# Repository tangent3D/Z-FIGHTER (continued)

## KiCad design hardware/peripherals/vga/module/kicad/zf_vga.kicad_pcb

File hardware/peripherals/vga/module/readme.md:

## Z-FIGHTER VGA Module

[Project Notes](https://tangent.space/vga.htm)

[PCB schematic](../../../../media/schematic_vga_module.pdf)

[PCB layout](../../../../media/layout_vga_module.pdf)

## Bill of Materials
|Reference|Description|Mouser #|Link
|--|--|--|--|
U1,U2|74HC4040||
U3,U4|GAL16V8||
U5,U6,U12,U13,U14|74HC541||
U7|74HC00||
U8|74HC04||
U9|74HC74||
U10|74HC165||
U11|AS6C6264||
X1|25.175 MHz Oscillator, DIP8/DIP14||
Q1|BC547, TO-92||
R1 - R3|220Ω Resistor, 1/4W||
R4 - R8|75Ω Resistor, 1/4W||
R9,R10|1KΩ Resistor, 1/4W||
C1,C2,C3,C6,C7|470pF Capacitor, Ceramic, 5mm||
C4,C5|22pF Capacitor, Ceramic, 5mm||
C8 - C22|0.1uF Capacitor, Ceramic, 5mm||
J1|26P Female Header, Vertical||
J2|8P Female Header, Vertical||
J3|DE-15 Female R/A||
J4,J5|DE-9 Male R/A||
SW1|DIP Switch, 3x, 7.62mm||
JP1|Jumper, 2.54mm, Vertical||

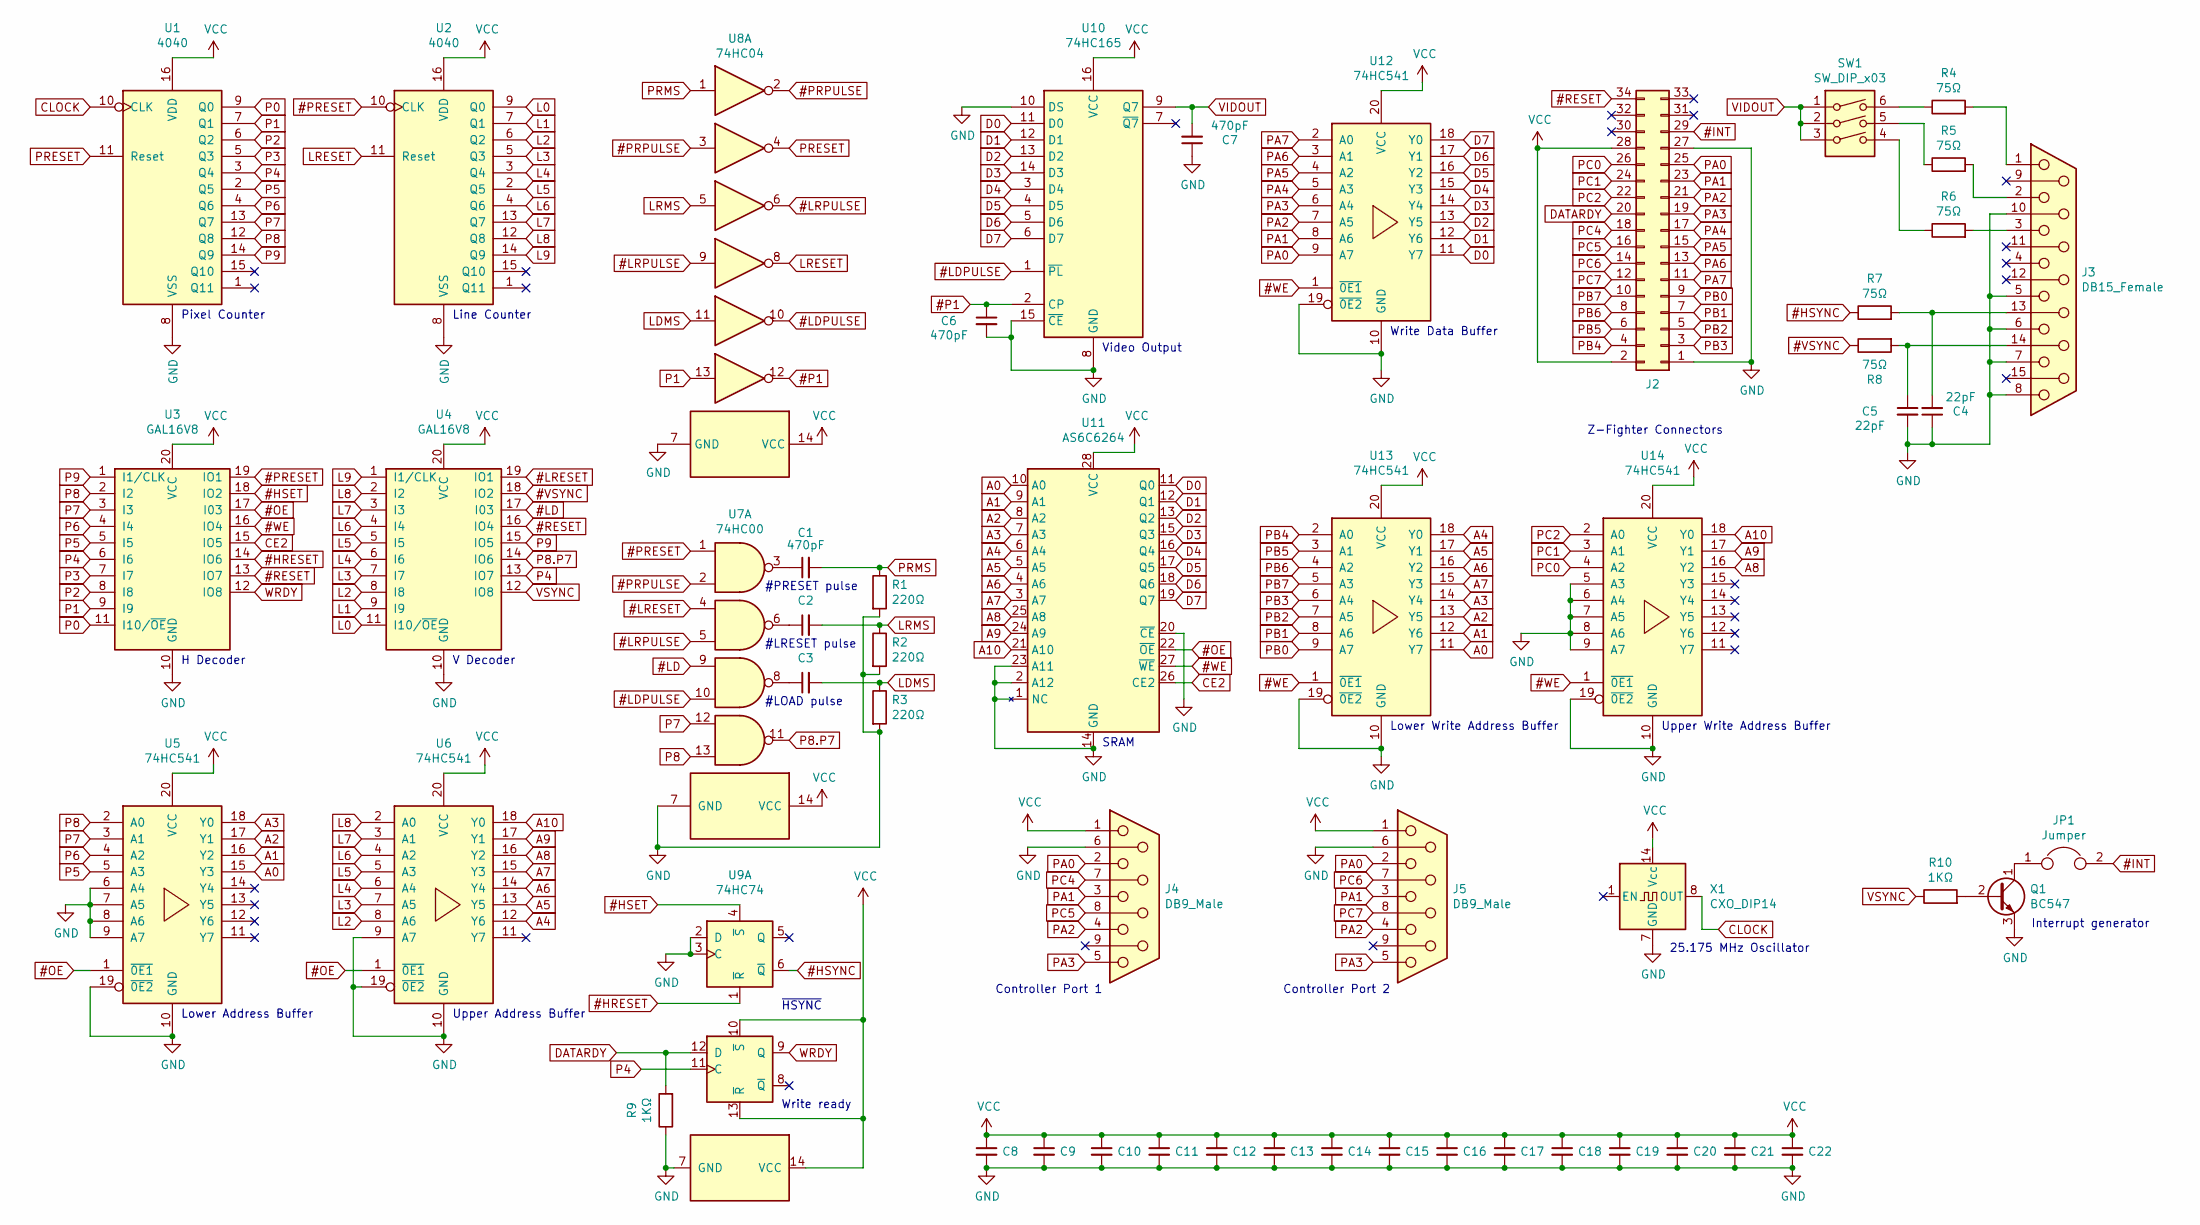
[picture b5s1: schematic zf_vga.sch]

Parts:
C1, C2, C3, C6, C7: 470pF; C_Disc_D7.5mm_W2.5mm_P5.00mm
C4, C5: 22pF; C_Disc_D7.5mm_W2.5mm_P5.00mm
C8, C9, C10, C11, C12, C13, C14, C15, C16, C17, C18, C19, C20, C21, C22: 0.1uF; C_Disc_D7.5mm_W2.5mm_P5.00mm
J2: Z-FIGHTER Expansion Port; Z-FIGHTER_Expansion_Port
J3: DB15_Female; DSUB-15-HD_Female_Horizontal_P2.29x1.98mm_EdgePinOffset8.35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
J4, J5: DB9_Male; DSUB-9_Male_Horizontal_P2.77x2.84mm_EdgePinOffset7.70mm_Hou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
JP1: Jumper
Q1: BC547; TO-92_Inline_Wide
R1, R2, R3: 220Ω; R_Axial_DIN0207_L6.3mm_D2.5mm_P7.62mm_Horizontal
R4, R5, R6, R7, R8: 75Ω; R_Axial_DIN0207_L6.3mm_D2.5mm_P7.62mm_Horizontal
R9, R10: 1KΩ; R_Axial_DIN0207_L6.3mm_D2.5mm_P7.62mm_Horizontal
SW1: SW_DIP_x03; DIP-6_W7.62mm_LongPads
U1, U2: 4040; DIP-16_W7.62mm_LongPads
U3, U4: GAL16V8; DIP-20_W7.62mm_LongPads
U5, U6, U12, U13, U14: 74HC541; DIP-20_W7.62mm_LongPads
U7: 74HC00; DIP-14_W7.62mm_LongPads
U8: 74HC04; DIP-14_W7.62mm_LongPads
U9: 74HC74; DIP-14_W7.62mm_LongPads
U10: 74HC165; DIP-16_W7.62mm_LongPads
U11: AS6C6264; DIP-28_W15.24mm_LongPads
X1: CXO_DIP14; Oscillator_DIP-14_LargePads

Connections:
#HRESET: U3.14 (IO6), U9.1 (~R)
#HSET: U3.18 (IO2), U9.4 (~S)
#HSYNC: R7.1, U9.6 (~Q)
#INT: J2.29, JP1.2
#LD: U4.17 (I03), U7.9
#LDPULSE: U7.10, U8.10, U10.1 (~PL)
#LRESET: U4.19 (IO1), U7.4
#LRPULSE: U7.5, U8.6, U8.9
#OE: U3.17 (I03), U5.1 (~0E1), U6.1 (~0E1), U11.22 (~OE)
#P1: C6.1, U8.12, U10.2 (CP)
#PRESET: U2.10 (CLK), U3.19 (IO1), U7.1
#PRPULSE: U7.2, U8.2, U8.3
#RESET: J2.34, U3.13 (IO7), U4.16 (IO4)
#VSYNC: R8.1, U4.18 (IO2)
#WE: U3.16 (IO4), U11.27 (~WE), U12.1 (~0E1), U13.1 (~0E1), U14.1 (~0E1)
A0: U5.15 (Y3), U11.10 (A0), U13.11 (Y7)
A1: U5.16 (Y2), U11.9 (A1), U13.12 (Y6)
A2: U5.17 (Y1), U11.8 (A2), U13.13 (Y5)
A3: U5.18 (Y0), U11.7 (A3), U13.14 (Y4)
A4: U6.12 (Y6), U11.6 (A4), U13.18 (Y0)
A5: U6.13 (Y5), U11.5 (A5), U13.17 (Y1)
A6: U6.14 (Y4), U11.4 (A6), U13.16 (Y2)
A7: U6.15 (Y3), U11.3 (A7), U13.15 (Y3)
A8: U6.16 (Y2), U11.25 (A8), U14.16 (Y2)
A9: U6.17 (Y1), U11.24 (A9), U14.17 (Y1)
A10: U6.18 (Y0), U11.21 (A10), U14.18 (Y0)
CE2: U3.15 (IO5), U11.26 (CE2)
CLOCK: U1.10 (CLK), X1.5, X1.8 (OUT); also elsewhere on the board
D0: U10.11 (D0), U11.11 (Q0), U12.11 (Y7)
D1: U10.12 (D1), U11.12 (Q1), U12.12 (Y6)
D2: U10.13 (D2), U11.13 (Q2), U12.13 (Y5)
D3: U10.14 (D3), U11.15 (Q3), U12.14 (Y4)
D4: U10.3 (D4), U11.16 (Q4), U12.15 (Y3)
D5: U10.4 (D5), U11.17 (Q5), U12.16 (Y2)
D6: U10.5 (D6), U11.18 (Q6), U12.17 (Y1)
D7: U10.6 (D7), U11.19 (Q7), U12.18 (Y0)
DATARDY: J2.20, R9.2, U9.12 (D)
GND: C4.1, C5.2, C6.2, C7.1, C8.2, C9.2, C10.2, C11.2, C12.2, C13.2, C14.2, C15.2, C16.2, C17.2, C18.2, C19.2, C20.2, C21.2, C22.2, J2.1, J2.27, J3.5, J3.6, J3.7, J3.8, J3.10, J4.6, J5.6, Q1.3 (E), R1.2, R2.2, R3.2, R9.1, U1.8 (VSS), U2.8 (VSS), U3.10 (GND), U4.10 (GND), U5.6 (A4), U5.7 (A5), U5.8 (A6), U5.9 (A7), U5.10 (GND), U5.19 (~0E2), U6.9 (A7), U6.10 (GND), U6.19 (~0E2), U7.7 (GND), U8.7 (GND), U9.2 (D), U9.3 (C), U9.7 (GND), U10.8 (GND), U10.10 (DS), U10.15 (~CE), U11.1 (NC), U11.2 (A12), U11.14 (GND), U11.20 (~CE), U11.23 (A11), U12.10 (GND), U12.19 (~0E2), U13.10 (GND), U13.19 (~0E2), U14.5 (A3), U14.6 (A4), U14.7 (A5), U14.8 (A6), U14.9 (A7), U14.10 (GND), U14.19 (~0E2), X1.4, X1.7 (GND); also elsewhere on the board
L0: U2.9 (Q0), U4.11 (I10/~OE~)
L1: U2.7 (Q1), U4.9 (I9)
L2: U2.6 (Q2), U4.8 (I8), U6.8 (A6)
L3: U2.5 (Q3), U4.7 (I7), U6.7 (A5)
L4: U2.3 (Q4), U4.6 (I6), U6.6 (A4)
L5: U2.2 (Q5), U4.5 (I5), U6.5 (A3)
L6: U2.4 (Q6), U4.4 (I4), U6.4 (A2)
L7: U2.13 (Q7), U4.3 (I3), U6.3 (A1)
L8: U2.12 (Q8), U4.2 (I2), U6.2 (A0)
L9: U2.14 (Q9), U4.1 (I1/CLK)
LDMS: C3.2, R3.1, U8.11
LRESET: U2.11 (Reset), U8.8
LRMS: C2.2, R2.1, U8.5
unnamed: C1.1, U7.3
unnamed: C2.1, U7.6
unnamed: C3.1, U7.8
unnamed: C4.2, J3.13, R7.2
unnamed: C5.1, J3.14, R8.2
unnamed: J3.1, R4.2
unnamed: J3.2, R5.2
unnamed: J3.3, R6.2
unnamed: JP1.1, Q1.1 (C)
unnamed: Q1.2 (B), R10.2
unnamed: R4.1, SW1.6
unnamed: R5.1, SW1.5
unnamed: R6.1, SW1.4
P0: U1.9 (Q0), U3.11 (I10/~OE~)
P1: U1.7 (Q1), U3.9 (I9), U8.13
P2: U1.6 (Q2), U3.8 (I8)
P3: U1.5 (Q3), U3.7 (I7)
P4: U1.3 (Q4), U3.6 (I6), U4.13 (IO7), U9.11 (C)
P5: U1.2 (Q5), U3.5 (I5), U5.5 (A3)
P6: U1.4 (Q6), U3.4 (I4), U5.4 (A2)
P7: U1.13 (Q7), U3.3 (I3), U5.3 (A1), U7.12
P8: U1.12 (Q8), U3.2 (I2), U5.2 (A0), U7.13
P8.P7: U4.14 (IO6), U7.11
P9: U1.14 (Q9), U3.1 (I1/CLK), U4.15 (IO5)
PA0: J2.25, J4.2, J5.2, U12.9 (A7)
PA1: J2.23, J4.3, J5.3, U12.8 (A6)
PA2: J2.21, J4.4, J5.4, U12.7 (A5)
PA3: J2.19, J4.5, J5.5, U12.6 (A4)
PA4: J2.17, U12.5 (A3)
PA5: J2.15, U12.4 (A2)
PA6: J2.13, U12.3 (A1)
PA7: J2.11, U12.2 (A0)
PB0: J2.9, U13.9 (A7)
PB1: J2.7, U13.8 (A6)
PB2: J2.5, U13.7 (A5)
PB3: J2.3, U13.6 (A4)
PB4: J2.4, U13.2 (A0)
PB5: J2.6, U13.3 (A1)
PB6: J2.8, U13.4 (A2)
PB7: J2.10, U13.5 (A3)
PC0: J2.26, U14.4 (A2)
PC1: J2.24, U14.3 (A1)
PC2: J2.22, U14.2 (A0)
PC4: J2.18, J4.7
PC5: J2.16, J4.8
PC6: J2.14, J5.7
PC7: J2.12, J5.8
PRESET: U1.11 (Reset), U8.4
PRMS: C1.2, R1.1, U8.1
VCC: C8.1, C9.1, C10.1, C11.1, C12.1, C13.1, C14.1, C15.1, C16.1, C17.1, C18.1, C19.1, C20.1, C21.1, C22.1, J2.2, J2.28, J4.1, J5.1, U1.16 (VDD), U2.16 (VDD), U3.20 (VCC), U4.20 (VCC), U5.20 (VCC), U6.20 (VCC), U7.14 (VCC), U8.14 (VCC), U9.10 (~S), U9.13 (~R), U9.14 (VCC), U10.16 (VCC), U11.28 (VCC), U12.20 (VCC), U13.20 (VCC), U14.20 (VCC), X1.14 (Vcc); also elsewhere on the board
VIDOUT: C7.2, SW1.1, SW1.2, SW1.3, U10.9 (Q7)
VSYNC: R10.1, U4.12 (IO8)
WRDY: U3.12 (IO8), U9.9 (Q)

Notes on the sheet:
Line Counter
SRAM
Write ready
~HSYNC
Video Output
Controller Port 2
Controller Port 1
Lower Write Address Buffer
Upper Write Address Buffer
Z-Fighter Connectors
25.175 MHz Oscillator
Upper Address Buffer
Lower Address Buffer
V Decoder
H Decoder
#PRESET pulse
#LRESET pulse
Write Data Buffer
Pixel Counter
Interrupt generator
#LOAD pulse

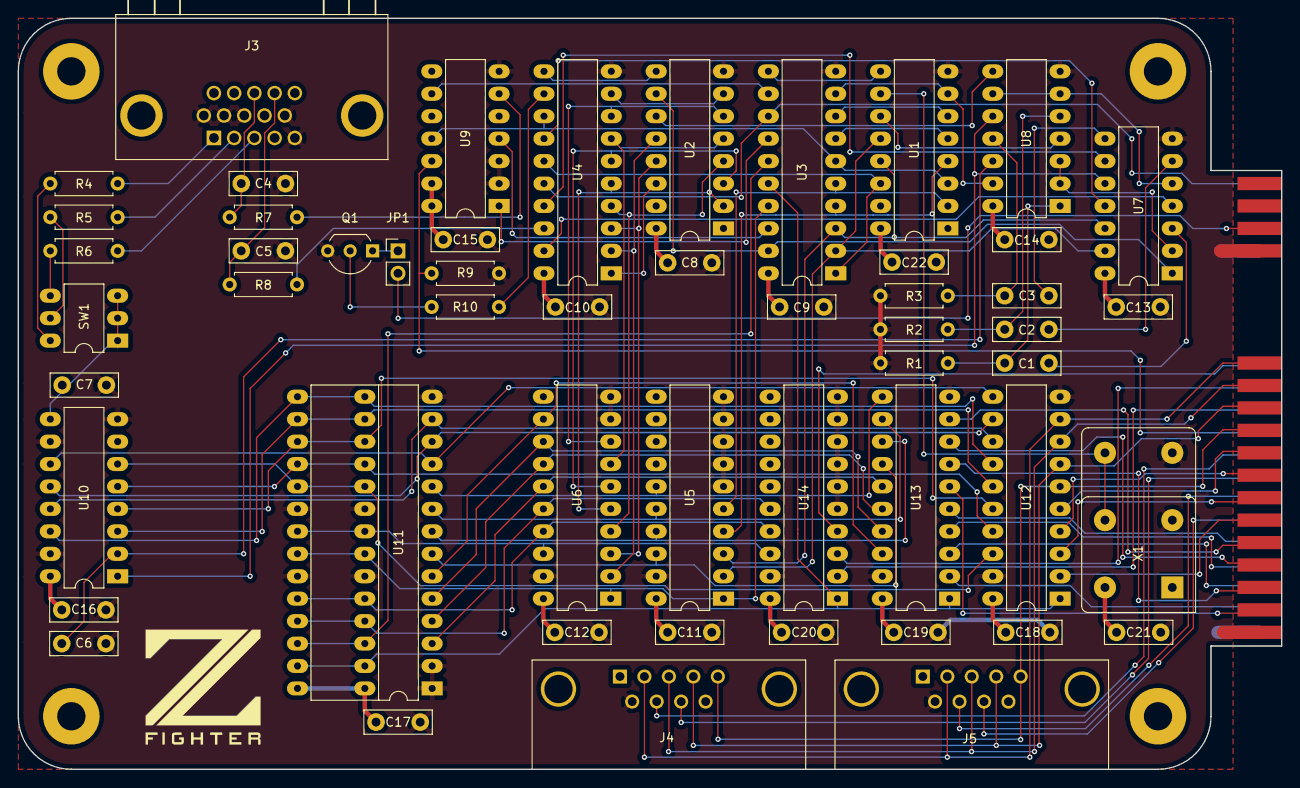
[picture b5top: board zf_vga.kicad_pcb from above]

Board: 2 copper layers, 143.0 x 85.0 mm, 59 parts (0 on the bottom side), 104 nets.

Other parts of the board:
Mount1, Mount2, Mount3, Mount4: MountingHole_3.2mm_M3_Pad
X1#2: CXO_DIP14; Oscillator_DIP-14_LargePads

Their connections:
CLOCK: X1#2.8; also elsewhere on the board
GND: X1#2.7; also elsewhere on the board
VCC: X1#2.14; also elsewhere on the board

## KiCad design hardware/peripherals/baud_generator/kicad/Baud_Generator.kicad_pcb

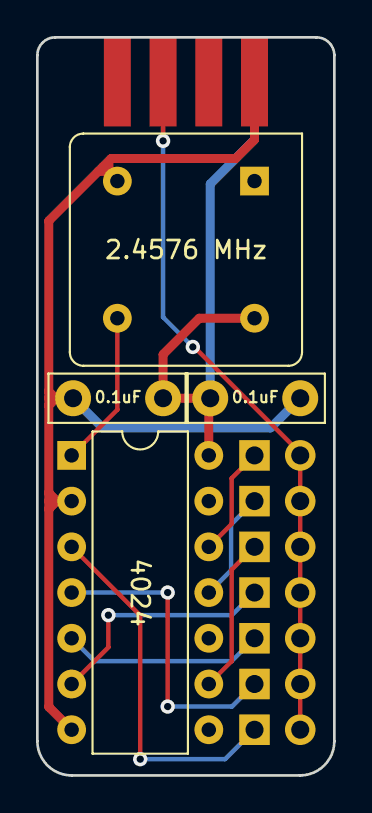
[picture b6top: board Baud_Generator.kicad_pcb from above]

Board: 2 copper layers, 16.5 x 41.0 mm, 6 parts (0 on the bottom side), 11 nets.

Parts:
0.1uF: 0.1uF; C_Disc_D7.5mm_W2.5mm_P5.00mm
C2: 0.1uF; C_Disc_D7.5mm_W2.5mm_P5.00mm
J1: Conn_02x04_Odd_Even; ZF_CPU_Control_Header
J2: Conn_02x07_Odd_Even; PinHeader_2x07_P2.54mm_Vertical
U1: 4024; DIP-14_W7.62mm
X1: 2.4576 MHz; Oscillator_DIP-8

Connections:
CLOCK2: J1.5, J2.2, J2.4, J2.6, J2.8, J2.10, J2.12, J2.14
GND: 0.1uF.2, C2.2, J1.1, U1.2, U1.7, X1.4
unnamed: J2.1, U1.12
unnamed: J2.3, U1.11
unnamed: J2.5, U1.9
unnamed: J2.7, U1.6
unnamed: J2.9, U1.5
unnamed: J2.11, U1.4
unnamed: J2.13, U1.3
unnamed: U1.1, X1.5
VCC: 0.1uF.1, C2.1, J1.2, U1.14, X1.8

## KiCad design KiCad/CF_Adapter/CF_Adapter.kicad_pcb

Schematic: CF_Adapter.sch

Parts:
J1: Z-Fighter IDE Connector; PinHeader_2x20_P2.54mm_Vertical
J2: Conn_02x25_Top_Bottom; CF-Card_3M_N7E50-7516PK-20-WF
R1: 1KΩ; R_1206_3216Metric_Pad1.30x1.75mm_HandSolder

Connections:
#CFCS: J1.37, J2.7
#RD: J1.25, J2.34
#RESET: J1.1, J2.41
#WR: J1.23, J2.35
A0: J1.35, J2.20
A1: J1.33, J2.19
A2: J1.36, J2.18
D0: J1.17, J2.21
D1: J1.15, J2.22
D2: J1.13, J2.23
D3: J1.11, J2.2
D4: J1.9, J2.3
D5: J1.7, J2.4
D6: J1.5, J2.5
D7: J1.3, J2.6
GND: J1.2, J1.19, J1.22, J1.24, J1.26, J1.30, J1.40, J2.1, J2.8, J2.9, J2.10, J2.11, J2.12, J2.14, J2.15, J2.16, J2.17, J2.39, J2.50
unnamed: J2.36, R1.2
PATA29: J1.29, J2.44
PATA34: J1.34, J2.46
PATA38: J1.38, J2.32
VCC: J1.20, J2.13, J2.38, R1.1

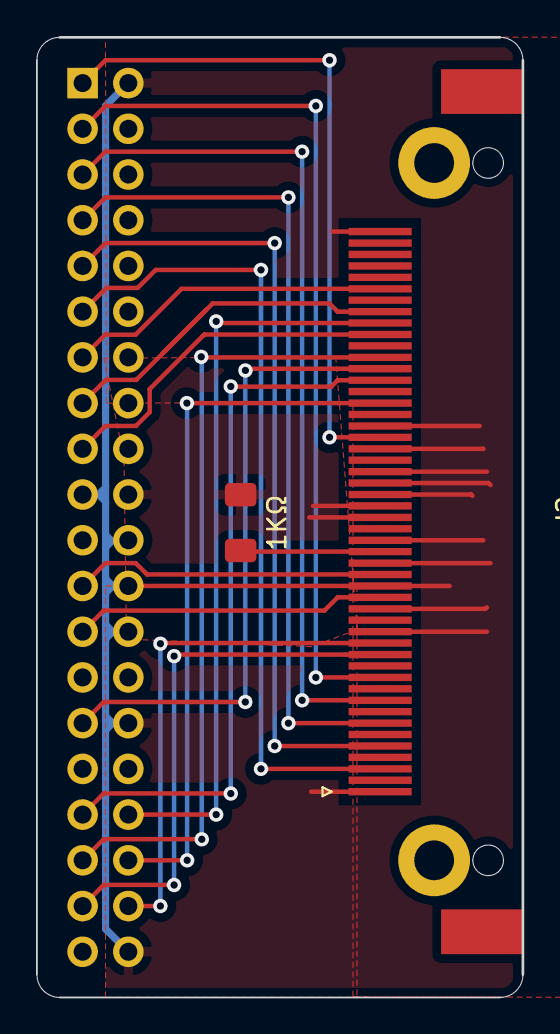
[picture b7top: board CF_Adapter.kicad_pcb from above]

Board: 2 copper layers, 27.0 x 53.3 mm, 3 parts (0 on the bottom side), 21 nets.

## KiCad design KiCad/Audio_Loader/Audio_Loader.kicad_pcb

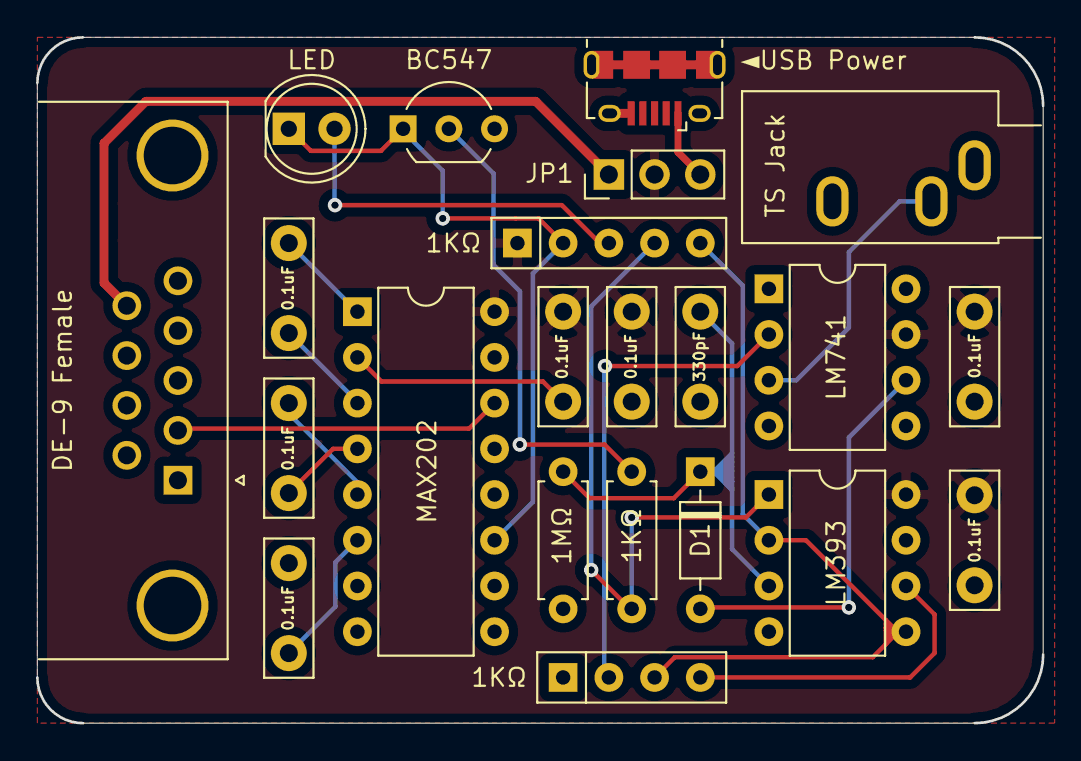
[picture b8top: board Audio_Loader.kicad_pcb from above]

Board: 2 copper layers, 55.9 x 38.1 mm, 22 parts (0 on the bottom side), 21 nets.

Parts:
C1, C2, C3, C5, C6, C7, C8: 0.1uF; C_Disc_D7.5mm_W2.5mm_P5.00mm
C4: 330pF; C_Disc_D7.5mm_W2.5mm_P5.00mm
D1: 1N4148; D_DO-35_SOD27_P7.62mm_Horizontal
D2: LED; LED_D5.0mm
J1: ◄USB Power; USB_Micro-B_Amphenol_10118194_Horizontal
J2: DE-9 Female; DSUB-9_Female_Horizontal_P2.77x2.84mm_EdgePinOffset4.94mm_H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
J3: TS Jack; Jack_3.5mm_CUI_SJ1-3533NG_Horizontal
JP1: Jumper_3_Open; PinHeader_1x03_P2.54mm_Vertical
Q1: BC547; TO-92_Inline_Wide
R1: 1MΩ; R_Axial_DIN0207_L6.3mm_D2.5mm_P7.62mm_Horizontal
R3: 1KΩ; R_Axial_DIN0207_L6.3mm_D2.5mm_P7.62mm_Horizontal
RN1: 1KΩ; R_Array_SIP5
RN2: 1KΩ; R_Array_SIP4
U1: LM741; DIP-8_W7.62mm
U2: LM393; DIP-8_W7.62mm
U3: MAX202; DIP-16_W7.62mm

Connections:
GND: C1.2, C2.2, C3.2, C4.1, C8.2, J1.5, J1.6, J2.0, J2.5, J3.S, Q1.3, R1.2, RN2.1, U1.4, U2.4, U3.15
unnamed: C4.2, D1.1, R1.1, U2.3
unnamed: C5.1, U3.3
unnamed: C5.2, U3.1
unnamed: C6.2, U3.2
unnamed: C7.1, U3.4
unnamed: C7.2, U3.5
unnamed: C8.1, U3.6
unnamed: D1.2, U1.6
unnamed: J1.1, JP1.3
unnamed: J2.2, U3.14
unnamed: J3.T, U1.3
unnamed: Q1.2, R3.2
PIN_9: J2.9, JP1.1
RN1a: RN1.5, RN2.3, U2.2, U2.5
RN1b: R3.1, RN1.4, U2.1
RN1c: D2.1, Q1.1, RN1.2, U3.11
RN1d: D2.2, RN1.3
RN2a: RN2.2, U1.2
RN2c: RN2.4, U2.6
VCC: C1.1, C2.1, C3.1, C6.1, JP1.2, RN1.1, U1.7, U2.8, U3.16

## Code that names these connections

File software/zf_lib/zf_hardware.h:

// Hardware definitions for Z-Fighter
// by Tangent 2021

#ifndef ZF_HARDWARE_H
#define ZF_HARDWARE_H

#define ROMDISABLE_n    0x38

// 8255A Programmable Peripheral Interface (Accessory)
#define PPI_ACC         0x40
#define PORTA_ACC       PPI_ACC+0   // Connected to key switches
#define PORTB_ACC       PPI_ACC+1   // Connected to ST7920 LCD data bus
#define PORTC_ACC       PPI_ACC+2   // Connected to LCD control signals, backlight and buzzer
#define CTRL_ACC        PPI_ACC+3   // PPI control port

// BSR (Bit Set/Reset) control words (Accessory)
#define LCD_E_LO        0x00        // LCD E (Enable) low
#define LCD_E_HI        0x01        // LCD E (Enable) high
#define LCD_WR          0x02        // LCD R/#W low (Write)
#define LCD_RD          0x03        // LCD R/#W high (Read)
#define LCD_INST        0x04        // LCD RS low (Instruction)
#define LCD_DATA        0x05        // LCD RS high (Data)
#define LCD_BL_OFF      0x06        // LCD backlight off
#define LCD_BL_ON       0x07        // LCD backlight on
#define BUZZER_OFF      0x0E        // Electromagnetic buzzer off
#define BUZZER_ON       0x0F        // Electromagnetic buzzer on

// 8255A Programmable Peripheral Interface (User)
#define PPI_USER        0x80
#define PORTA           PPI_USER+1  // User port PA7-PA0
#define PORTB           PPI_USER+2  // User port PB7-PB0
#define PORTC           PPI_USER+3  // User port PC7-PC0
#define CTRL            PPI_USER+4  // User PPI control port

// Z80 SIO/0 Serial Input/Output Controller
#define SIO             0x00
#define SIO_A           SIO+0       // SIO channel A data port
#define SIO_B           SIO+1       // SIO channel B data port
#define SIO_AC          SIO+2       // SIO channel A control port
#define SIO_BC          SIO+3       // SIO channel B control port

// CompactFlash
#define CF0             0x10        // CF data I/O
#define CF1             CF0+1       // Error register (/RD), Feature (/WR)
#define CF2             CF0+2       // Sector count
#define CF3             CF0+3       // Sector address LBA 0 [0:7]
#define CF4             CF0+4       // Sector address LBA 1 [8:15]
#define CF5             CF0+5       // Sector address LBA 2 [16:23]
#define CF6             CF0+6       // Sector address LBA 3 [24:27 (LSB)]
#define CF7             CF0+7       // Status (/RD), Command (/WR)

#endif

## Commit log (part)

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2021-12-09 Removed user drawing
2021-12-09 added screenshot
2021-12-11 Preserve user's bet value after game reset
2021-12-11 added win preview
2021-12-11 win preview sound only
2021-12-11 win preview sound after rendering
2021-12-11 Poker game screenshots
2021-12-16 Removed %include%
2021-12-16 make wip
2021-12-17 Converting project to new build system
2021-12-17 Create Makefile
2021-12-17 Update Makefile
2021-12-17 Project Makefiles
2021-12-17 Fix for mixed C and ASM projects, lib
2021-12-18 Restored zf_init
2021-12-18 Text adjustments
2021-12-18 Text improvements
2021-12-18 Text changes
2021-12-18 Removed map file export from ASM-only projects
2021-12-18 Added libs target
2021-12-18 Fixed optimization
2021-12-18 Removed send from project Makefiles
2021-12-18 Project names
2021-12-19 Removed environment variable
2021-12-19 Renamed directories
2021-12-19 Revert "Renamed directories"
    This reverts commit 2d6ab31311081504c00b8e9ba1250417e2ed232e.
2021-12-19 gitignore
2021-12-19 Renamed dir
2021-12-19 /obj/ dir wip
2021-12-19 Revert "/obj/ dir wip"
    This reverts commit f2d5f38264b7aed1d5f022622e97ff321ad512b0.
2021-12-19 Clean and cleaner targets
2021-12-19 Project send targets
2021-12-21 Added missing forward slash
2021-12-21 Sleep library function
2021-12-21 Update Makefile
    Removed trailing forward slash from occurrences of $(zf_lib), fixing 'make libs' from src directory. Deprecated console output.
2021-12-21 Added trailing forward slash to $(zf_lib)
2021-12-23 Auto get path to Makefile, silenced all targets
2021-12-24 Reduced some lines
2021-12-24 Restored send target
2021-12-24 Removed $(ext)
2021-12-24 mechzoom: moved all private elements from .h to .c
2021-12-24 mechzoom: improved bgm function
2021-12-24 mechzoom: updated endscreen graphic
2021-12-26 zf_lib_test comments
2021-12-28 Add echo
2021-12-28 Reworked clean/cleaner targets
2021-12-29 Routing
2022-01-01 mechzoom: added missing includes
2022-01-01 mechzoom: added missing variables to .h
2022-01-01 Fixed clean target warnings
2022-01-01 mechzoom: removed bgm test, fixed mystery glitch
2022-01-01 mechzoom: fixed hp underflow when dying 2x in 1 frame
2022-01-09 Update CF_Adapter.kicad_pcb
    Flipped silkscreen to be right side up when installed in ZF
2022-01-10 Update Makefile
    Fixed and removed recursion from clean targets
2022-01-11 Restored CP/M support to build system
2022-01-12 CP/M target, standalone ASM target, bare target, cleanup, formatting
2022-01-12 Updated to use .ROM instead of .BIN to match z88dk change
2022-01-12 Changed mentions of ".bin" to ".rom"
2022-01-12 ASM target comments cleanup
2022-01-13 Renamed 'bin' target to 'rom'
    Updated project Makefiles. Fixed
2022-01-13 Deprecated bare target
2022-01-13 Added 'ram' target
2022-01-15 Solution for RAM and ROM targets
    Using a workaround, all 'ram' target compiles now produce a .bin file which can be sent to zf_loader with the 'send' target. All 'rom' target compiles produce a 16K .rom file which can be burned to Z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
2022-01-16 ORG data at 4000h for ROM model compiles
    Adjusted to fully use ZF's default memory map
2022-01-16 wip makefile documentation
2022-01-18 Case adjustment, schema update, layout image update, readme
2022-01-20 Stand modifications
    Reduced ZF height when placed in stand, increased width
2022-01-21 Reorganized directories and content
2022-01-22 moved gitattributes
2022-01-22 gerber files
2022-01-22 Changed connector footprint from 6 to 8 pins
2022-01-22 Added system clock to CPU control header
2022-01-22 nc HALT
2022-01-23 added mechzoom menu screenshot
2022-01-26 Baud generator Gerber files
2022-02-07 Changed 'Z' logo overhang hangle
2022-02-09 color abstraction change and clarification
2022-02-10 Option to invert all LCD graphics data output
2022-02-14 Changed SPLD code to GALasm syntax
2022-02-21 hsync and vsync pulses with SPLDs
2022-02-25 Generate test pattern
2022-02-28 Removed address counters
2022-02-28 Write circuit
2022-03-01 #HSYNC SR latch
2022-03-01 Added another NAND gate
2022-03-02 #LOAD pulse monostable circuit
2022-03-03 VRAM sharing, write timing
2022-03-04 Working design!
2022-03-04 Test program
2022-03-04 Moved
2022-03-05 Replaced write address latches with buffers
2022-03-05 4040 counter ICs
2022-03-06 Adjusted shift register load timings, synchronized pixel and line counters
2022-03-07 Changed /hsync to set/reset on flip flop, changed bus to /we and /oe
2022-03-09 Controller, VGA ports, adjusted write timings
2022-03-11 Slowed down WRDY flip-flop again
2022-03-11 Footprints
2022-03-11 Started PCB
2022-03-11 Bypass caps
2022-03-12 Expansion port footprint
2022-03-12 Board layout progress
2022-03-13 Connected #RESET from ZF
2022-03-16 Routing draft, changed SRAM NC pin to VCC
2022-03-17 Routing progress
2022-03-17 Routing, silkscreen
2022-03-17 Progress switching to 0.3mm via drill, 0.6mm via size
2022-03-17 Fix all via clearances for 0.3mm via drill, 0.6mm via diameter
2022-03-17 Routing tweaks
2022-03-17 Updated Gerber files
2022-03-17 Silkscreen tweak
2022-03-18 Reduced pins of SRAM footprint
2022-03-18 Silkscreen fixes
2022-03-18 Fixed SRAM decoupling
2022-03-18 Annotations
2022-03-23 Flipped headers in schema for easier reference
2022-03-25 Replaced VGA connector footprint
    KiCad library horizontal D-SUB 15 footprint uses incorrect pin spacing.
2022-03-25 Fixed SPLD inputs
2022-03-26 VGA library function
2022-03-26 Centered horizontal timings
2022-03-26 New function for LCD compatible VGA output
2022-03-27 Joystick test function
2022-03-27 Joy test software
2022-03-27 Removed vga test
2022-03-28 VGA Module Rev. 1
    Fixed noise issues, added pull-up resistor to DATARDY
2022-03-28 Moved VGA connector slightly
2022-03-30 Reduced VGA write loop by 3 cycles
2022-03-31 Controller project files
2022-03-31 Fixed edge cuts
2022-03-31 Final controller and Gerber files
2022-03-31 Rounded corners
2022-03-31 Moved Gerber files
2022-04-01 Moved components to back of board
2022-04-10 VGA Rev. 2
    Fixed VGA connector footprint, expanded joystick connectors for '241 buffer, added jumper-selectable interrupt generator
2022-04-11 Redesigned controller around '241 buffer, added 2 extra buttons, increased height of PCB, added DE-9 connector
2022-04-11 Silkscreen
2022-04-11 U1 footprint to LongPads
2022-04-25 Changed Q1 footprint
2022-04-25 Fixed WRDY pin
2022-04-25 Rudimentary joystick reading/testing
2022-04-27 VGA Controller enclosure files
2022-04-29 VGA module enclosure
2022-05-09 code formatting
2022-05-12 Fixed interrupt circuit, routing improvements
2022-05-12 Disable interrupts during buzzer routine
2022-05-13 Added interrupt pragmas and environment variables to Makefile
2022-05-13 Added vgaWrite() function for writing bytes to VGA VRAM
2022-08-05 Schematic media, fixes
2022-08-22 Removed test files
2022-12-05 CF register map
2022-12-21 fat driver dev preparation
2023-01-16 python script for clean/cleaner targets
2023-03-24 started work on fat16Init()
2023-03-31 continued work on fat16
2023-04-02 started work on cf menu
2023-04-02 continued work on cf menu
2023-04-05 Build, memory map changes
    Enforce ROM model compilation, switch ZF to 32K ROM, 32K RAM memory map, switch to z80com for serial transfer,
2023-04-05 Renamed zf_loader directory
2023-04-06 compiler error fix for dinos.c
2023-04-07 Fix return to caller on exit
2023-04-08 improved cls() performance
2023-04-08 updated performance stats
2023-04-08 asm syntax change
2023-04-09 changed jp to jr
2023-04-10 z80com/zf_loader changes, makefile changes
2023-04-13 Wait for CTS, poll SIO until CTS deasserted
2023-04-13 Rename 'rom' target to 'bin'
2023-04-14 Routing, plot, mainboard images
2023-04-14 Mainboard images
2023-04-14 PCBWay Gerber
2023-04-15 Change digi-key link to female DE-9
2023-04-16 USB serial/power module
2023-04-16 Update Makefile for USB serial/power module
2023-04-16 Fix images
2023-05-30 Initial commit of CompactFlash lib implementation
2023-08-16 Fixed broken hardware addresses
2023-08-16 Update clean.py
    Add .ram extension
2023-08-16 Update Makefile
    Whitespace/documentation
2023-08-16 Update zf_loader.asm
    Clean up a bit
2023-08-16 Update zf_loader.asm
    Add delay after waiting for CTS
2023-08-16 Update zf_sio.asm
    Add delay after waiting for CTS to allow for connected device readiness
2023-08-16 Init CF, read CF sector
2023-08-16 Remove broken files
2023-08-16 Update Makefile
    Corrected text
2023-08-16 SIO memory dump function
